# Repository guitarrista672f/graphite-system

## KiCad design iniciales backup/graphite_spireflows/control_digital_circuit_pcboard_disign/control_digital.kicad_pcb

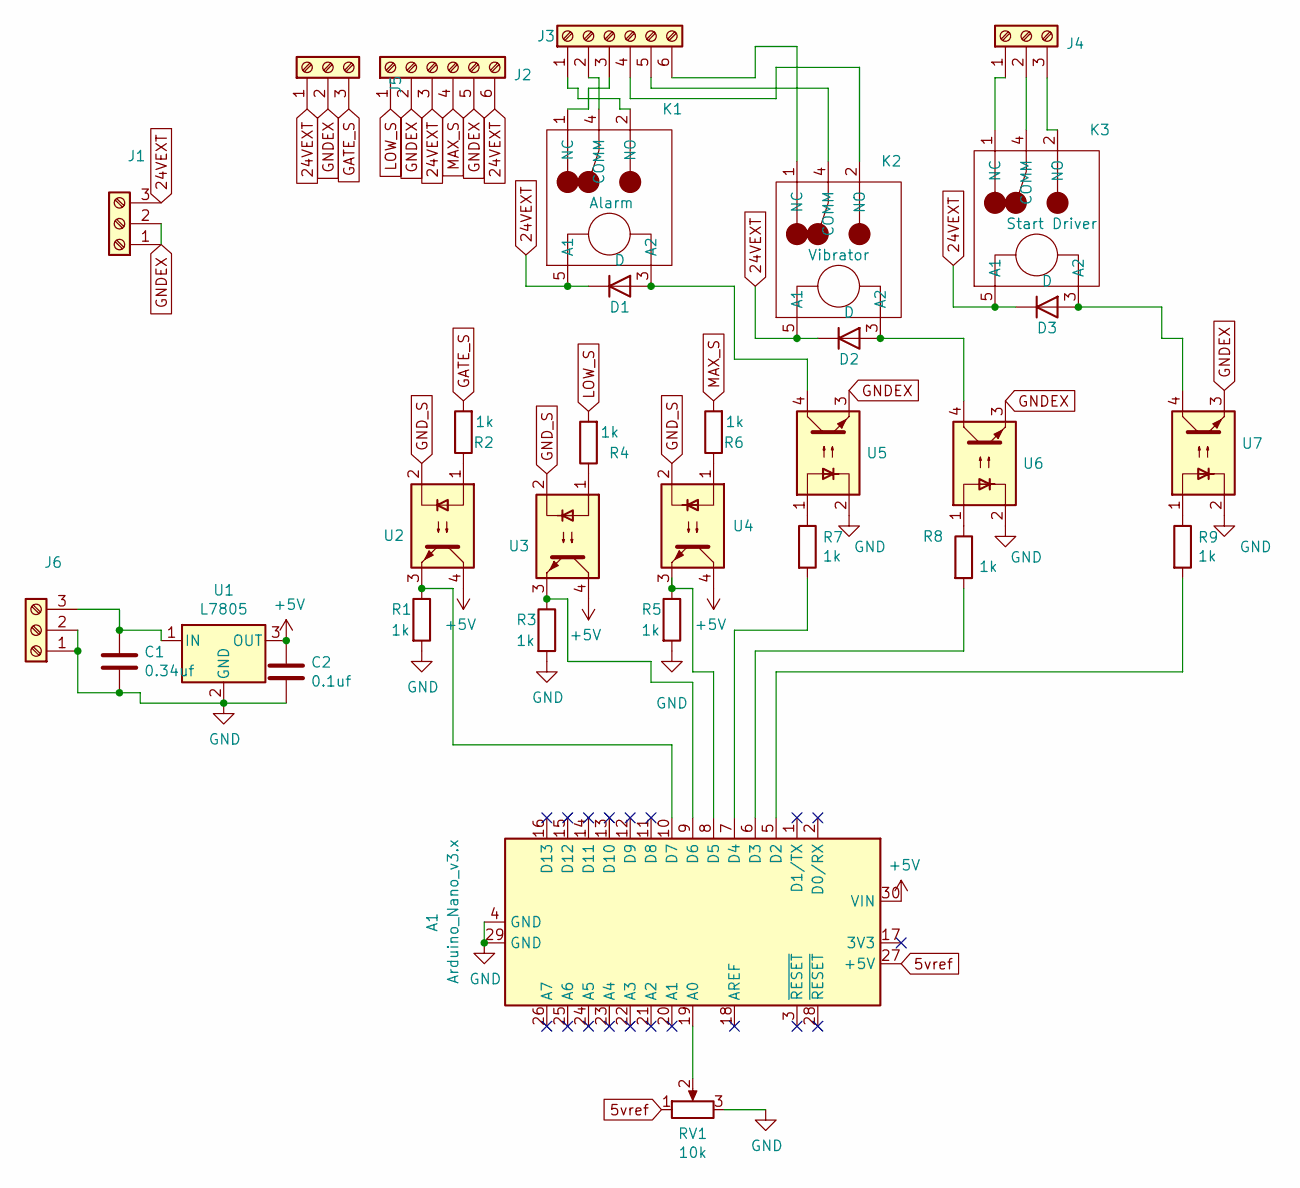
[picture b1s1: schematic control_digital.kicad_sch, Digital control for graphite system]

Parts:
A1: Arduino_Nano_v3.x; Arduino_Nano
C1: 0.34uf; CP_Radial_D6.3mm_P2.50mm
C2: 0.1uf; CP_Radial_D6.3mm_P2.50mm
D1, D2, D3: D; D_A-405_P7.62mm_Horizontal
J1, J4, J5, J6: Screw_Terminal_01x03; TerminalBlock_bornier-3_P5.08mm
J2, J3: Screw_Terminal_01x06; TerminalBlock_bornier-6_P5.08mm
K1: Alarm; SRD-24VDC-SL-C
K2: Vibrator; SRD-24VDC-SL-C
K3: Start Driver; SRD-24VDC-SL-C
R1, R2, R3, R4, R5, R6, R7, R8, R9: 1k; R_Axial_DIN0309_L9.0mm_D3.2mm_P12.70mm_Horizontal
RV1: 10k; pot_f
U1: L7805; Regulator7805
U2: SFH617A-2X016; DIP-4_W7.62mm
U3, U4, U5, U6, U7: SFH617A-2X016; DIP-4_W10.16mm

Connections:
5vref: A1.27 (+5V), RV1.1; also elsewhere on the board
24VEXT: D1.1 (K), D2.1 (K), D3.1 (K), J1.3, J2.3, J2.6, J5.1, K1.5 (A1), K2.5 (A1), K3.5 (A1)
+5V: A1.30 (VIN), C2.1, U1.3 (OUT), U2.4, U3.4, U4.4
GATE_S: J5.3, R2.2
GND: A1.4 (GND), A1.29 (GND), C1.2, C2.2, J6.1, J6.2, R1.2, R3.2, R5.2, RV1.3, U1.2 (GND), U5.2, U6.2, U7.2; also elsewhere on the board
GNDEX: J1.1, J1.2, J2.2, J2.5, J5.2, U5.3, U6.3, U7.3
GND_S: U2.2, U3.2, U4.2
LOW_S: J2.1, R4.2
MAX_S: J2.4, R6.2
unnamed: A1.5 (D2), R9.2
unnamed: A1.6 (D3), R8.2
unnamed: A1.7 (D4), R7.2
unnamed: A1.8 (D5), R5.1, U4.3
unnamed: A1.9 (D6), R3.1, U3.3
unnamed: A1.10 (D7), R1.1, U2.3
unnamed 15: A1.19 (A0), RV1.2; also elsewhere on the board
unnamed: C1.1, J6.3, U1.1 (IN)
unnamed: D1.2 (A), K1.3 (A2), U5.4
unnamed: D2.2 (A), K2.3 (A2), U6.4
unnamed: D3.2 (A), K3.3 (A2), U7.4
unnamed: J3.1, K1.2 (NO)
unnamed: J3.2, K1.4 (COMM)
unnamed: J3.3, K1.1 (NC)
unnamed: J3.4, K2.2 (NO)
unnamed: J3.5, K2.4 (COMM)
unnamed: J3.6, K2.1 (NC)
unnamed: J4.1, K3.1 (NC)
unnamed: J4.2, K3.4 (COMM)
unnamed: J4.3, K3.2 (NO)
unnamed: R2.1, U2.1
unnamed: R4.1, U3.1
unnamed: R6.1, U4.1
unnamed: R7.1, U5.1
unnamed: R8.1, U6.1
unnamed: R9.1, U7.1

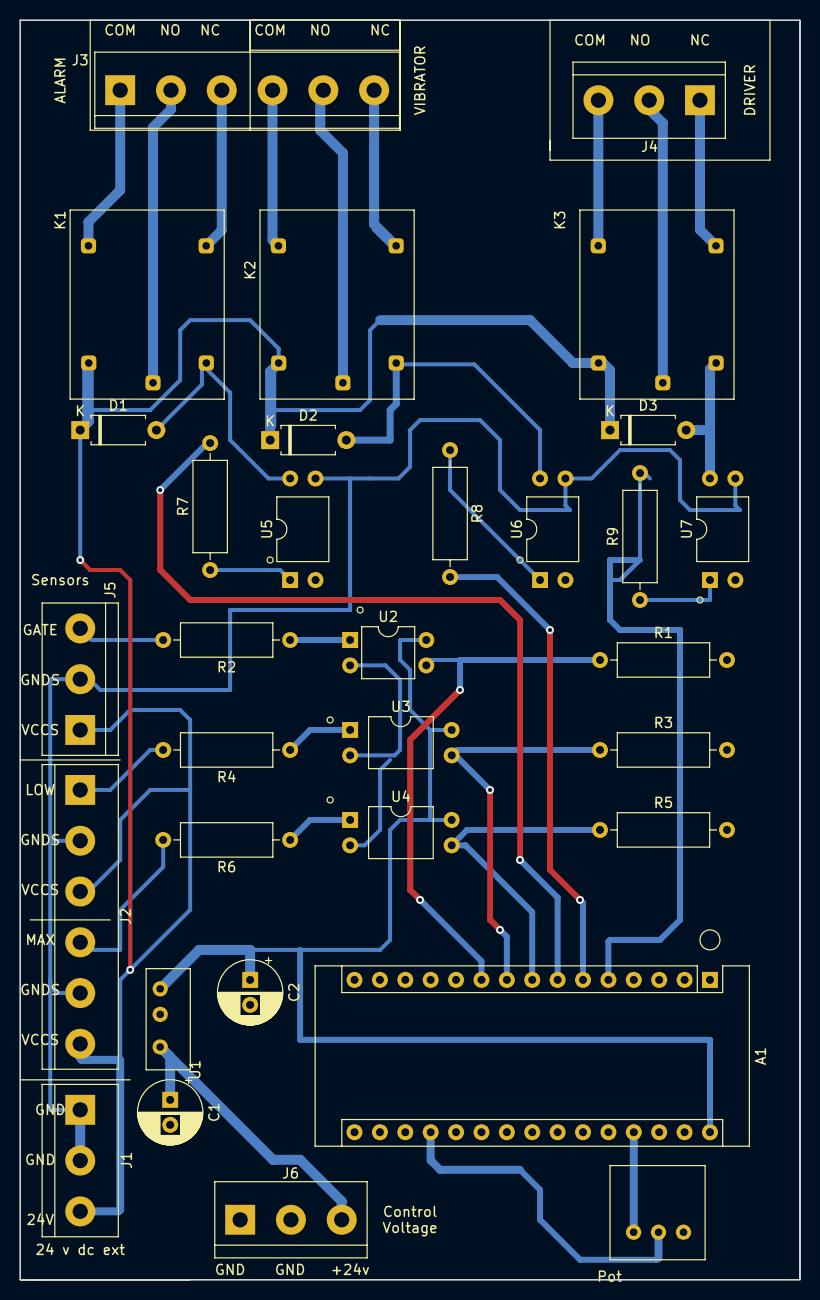
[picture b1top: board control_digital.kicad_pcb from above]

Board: 2 copper layers, 78.0 x 126.0 mm, 32 parts (0 on the bottom side), 35 nets.

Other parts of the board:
Pot: 10k; pot_f

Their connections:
5vref: Pot.1; also elsewhere on the board
GND: Pot.3; also elsewhere on the board
unnamed 15: Pot.2; also elsewhere on the board

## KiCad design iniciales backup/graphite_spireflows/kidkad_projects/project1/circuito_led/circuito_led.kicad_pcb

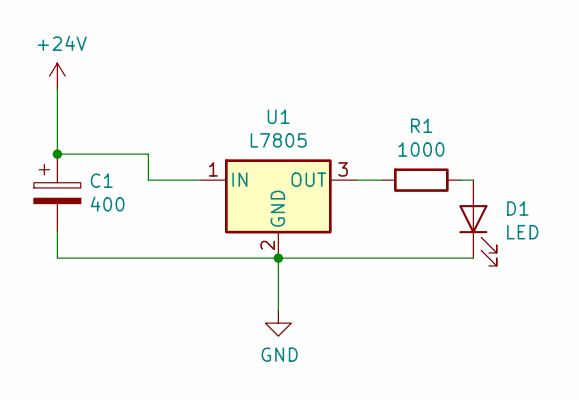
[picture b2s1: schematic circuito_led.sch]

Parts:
C1: 400; CP_Radial_D10.0mm_P3.50mm
D1: LED; LED_Oval_W5.2mm_H3.8mm
R1: 1000; R_Radial_Power_L16.1mm_W9.0mm_P7.37mm
U1: L7805; TO-220-3_Vertical

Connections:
+24V: C1.1, U1.1 (IN)
GND: C1.2, D1.1 (K), U1.2 (GND)
unnamed: D1.2 (A), R1.1
unnamed: R1.2, U1.3 (OUT)

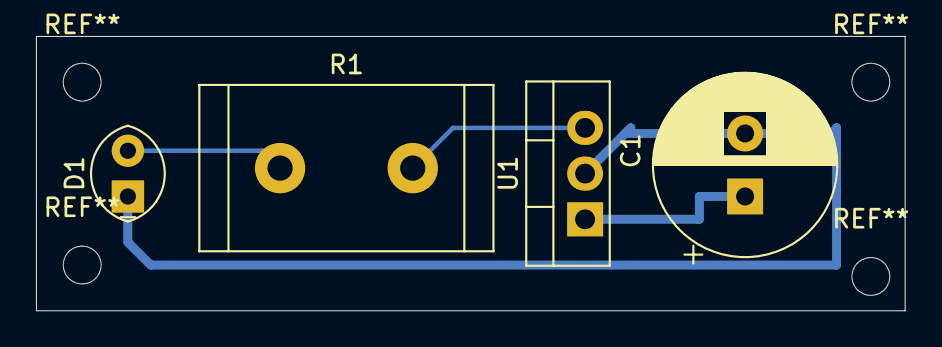
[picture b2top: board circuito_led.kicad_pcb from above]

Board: 2 copper layers, 48.3 x 15.2 mm, 4 parts (0 on the bottom side), 4 nets.

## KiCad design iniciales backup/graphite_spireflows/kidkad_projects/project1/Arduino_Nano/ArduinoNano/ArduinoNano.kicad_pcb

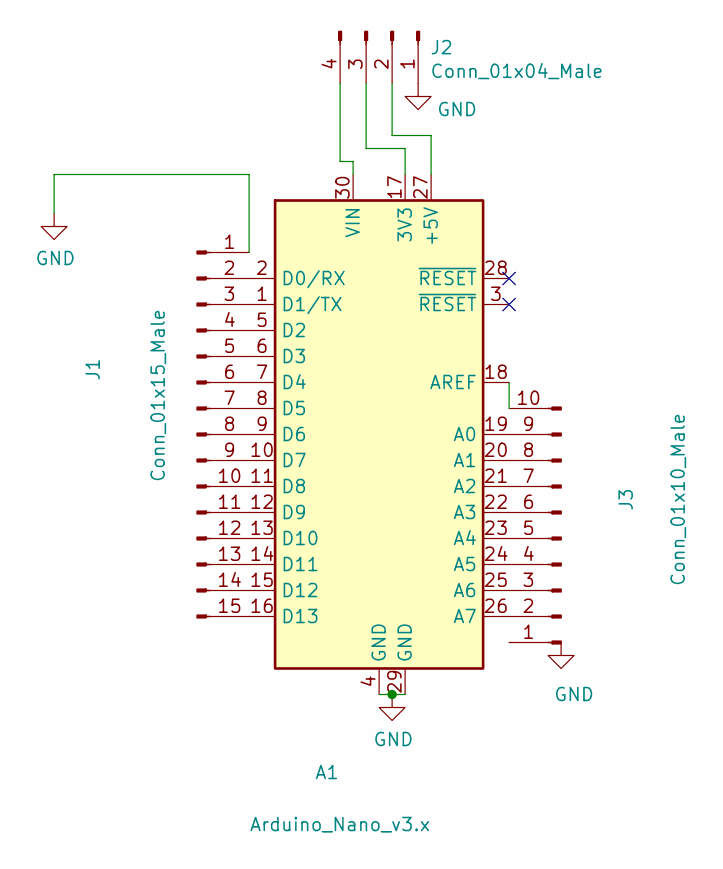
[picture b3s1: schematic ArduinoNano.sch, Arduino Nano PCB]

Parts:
A1: Arduino_Nano_v3.x; Arduino_Nano_WithMountingHoles
J1: Conn_01x15_Male; PinHeader_1x15_P2.54mm_Vertical
J2: Conn_01x04_Male; PinHeader_1x04_P2.54mm_Vertical
J3: Conn_01x10_Male; PinHeader_1x10_P2.54mm_Vertical

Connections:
GND: A1.4 (GND), A1.29 (GND), J1.1, J2.1
unnamed: A1.1 (D1/TX), J1.3
unnamed: A1.2 (D0/RX), J1.2
unnamed: A1.5 (D2), J1.4
unnamed: A1.6 (D3), J1.5
unnamed: A1.7 (D4), J1.6
unnamed: A1.8 (D5), J1.7
unnamed: A1.9 (D6), J1.8
unnamed: A1.10 (D7), J1.9
unnamed: A1.11 (D8), J1.10
unnamed: A1.12 (D9), J1.11
unnamed: A1.13 (D10), J1.12
unnamed: A1.14 (D11), J1.13
unnamed: A1.15 (D12), J1.14
unnamed: A1.16 (D13), J1.15
unnamed: A1.17 (3V3), J2.3
unnamed: A1.18 (AREF), J3.10
unnamed: A1.19 (A0), J3.9
unnamed: A1.20 (A1), J3.8
unnamed: A1.21 (A2), J3.7
unnamed: A1.22 (A3), J3.6
unnamed: A1.23 (A4), J3.5
unnamed: A1.24 (A5), J3.4
unnamed: A1.25 (A6), J3.3
unnamed: A1.26 (A7), J3.2
unnamed: A1.27 (+5V), J2.2
unnamed: A1.30 (VIN), J2.4

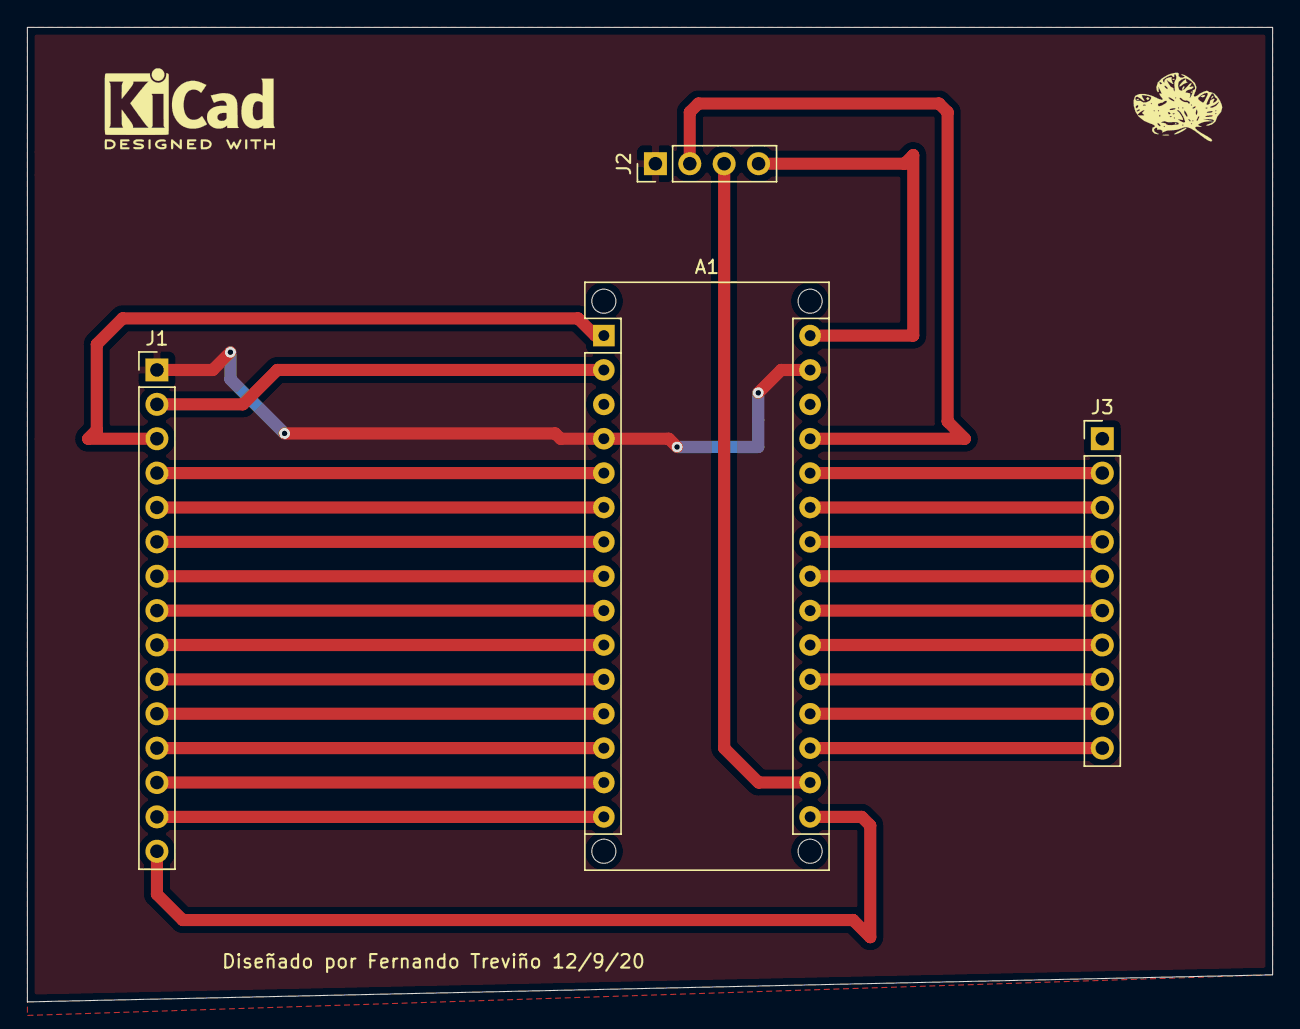
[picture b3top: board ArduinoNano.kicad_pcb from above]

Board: 2 copper layers, 92.0 x 72.0 mm, 5 parts (0 on the bottom side), 27 nets.

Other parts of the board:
ft: fam1; logo

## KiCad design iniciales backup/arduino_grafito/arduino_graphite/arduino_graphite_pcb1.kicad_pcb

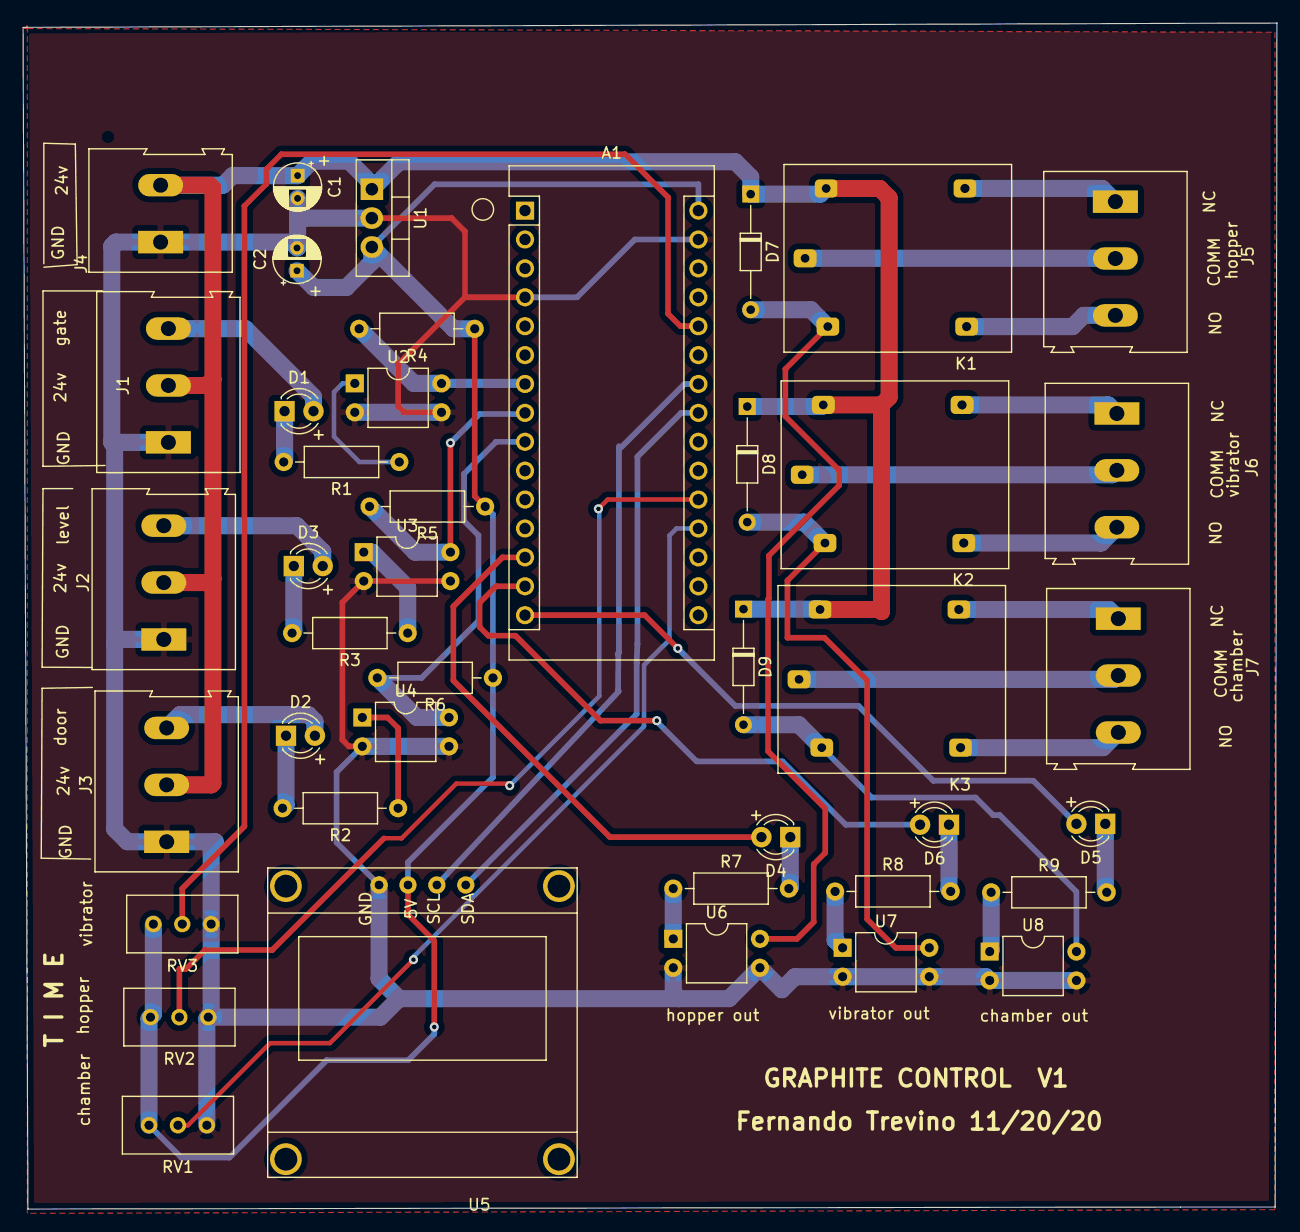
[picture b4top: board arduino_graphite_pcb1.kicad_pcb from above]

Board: 2 copper layers, 110.2 x 104.2 mm, 42 parts (0 on the bottom side), 41 nets.

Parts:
A1: Arduino_Nano_v3.x; Arduino_Nano
C1, C2: CP; capacitor
D1, D2, D3, D4, D5, D6: LED; led
D7, D8, D9: D; diode
J1, J2, J3, J5, J6, J7: Screw_Terminal_01x03; TerminalBlock_Altech_AK300-3_P5.00mm
J4: Screw_Terminal_01x02; TerminalBlock_Altech_AK300-2_P5.00mm
K1, K2, K3: srd24
R1, R2, R3, R7, R8, R9: 10k; resistor
R4, R5, R6: 1k; resistor
RV1, RV2, RV3: 1k; potensiometro
U1: L7805; 7805
U2, U3, U4, U6, U7, U8: EL817; DIP-4_W7.62mm
U5: ssd1306128x64

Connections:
+5vdc: A1.30, C2.1, R4.1, R5.1, R6.1, RV1.1, RV2.1, RV3.1, U1.3, U5.2
+24vdc: C1.1, D7.1, D8.1, D9.1, J1.2, J2.2, J3.2, J4.2, K1.1, K2.1, K3.1, U1.1
A1: A1.20, RV2.2
A4: A1.23, U5.4
A5: A1.24, U5.3
A7: A1.26, RV3.2
Ao: A1.19, RV1.2
GND: A1.4, A1.29, C1.2, C2.2, J1.1, J2.1, J3.1, J4.1, RV1.3, RV2.3, RV3.3, U1.2, U2.2, U2.3, U3.2, U3.3, U4.2, U4.3, U5.1, U6.2, U6.3, U7.2, U7.3, U8.2, U8.3
unnamed: D1.1, R1.2
unnamed: D1.2, J1.3
unnamed: D2.1, R2.2
unnamed: D2.2, J3.3
unnamed: D3.1, R3.2
unnamed: D3.2, J2.3
unnamed: D4.1, R7.2
unnamed: D5.1, R9.2
unnamed: D6.1, R8.2
unnamed: D7.2, K1.2, U6.4
unnamed: D8.2, K2.2, U7.4
unnamed: D9.2, K3.2, U8.4
unnamed: J5.1, K1.3
unnamed: J5.2, K1.4
unnamed: J5.3, K1.5
unnamed: J6.1, K2.3
unnamed: J6.2, K2.4
unnamed: J6.3, K2.5
unnamed: J7.1, K3.3
unnamed: J7.2, K3.4
unnamed: J7.3, K3.5
unnamed: R1.1, U2.1
unnamed: R2.1, U4.1
unnamed: R3.1, U3.1
unnamed: R7.1, U6.1
unnamed: R8.1, U7.1
unnamed: R9.1, U8.1
gate_hopper: A1.7, R4.2, U2.4
level_chamber: A1.8, R5.2, U3.4
out_chamber: A1.15, D5.2
out_hopper: A1.13, D4.2
out_vibrator: A1.14, D6.2
safety_doors: A1.9, R6.2, U4.4

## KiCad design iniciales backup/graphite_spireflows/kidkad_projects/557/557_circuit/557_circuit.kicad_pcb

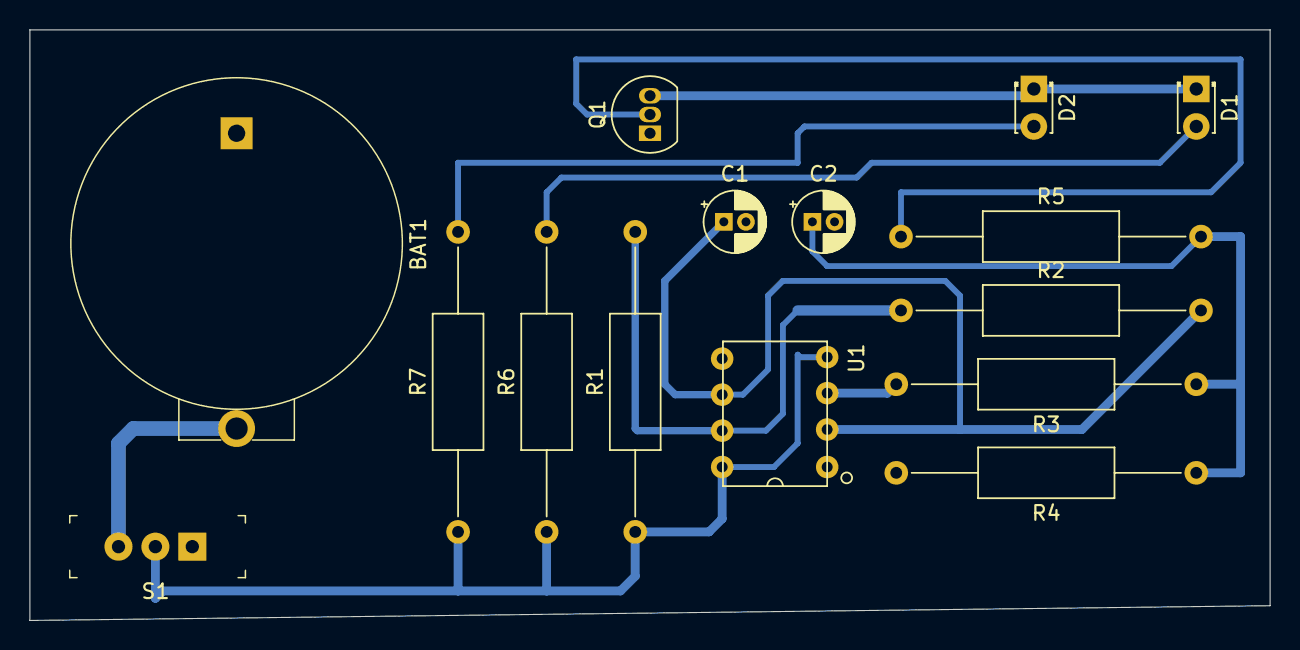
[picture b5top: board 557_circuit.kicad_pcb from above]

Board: 2 copper layers, 84.0 x 40.0 mm, 15 parts (0 on the bottom side), 11 nets.

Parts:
BAT1: BS-7; Battery_Holder_Coin_2032_BS-7
C1: 10uf; CP_Radial_D4.0mm_P1.50mm
C2: 100uf; CP_Radial_D4.0mm_P1.50mm
D1, D2: LED; LED_D1.8mm_W3.3mm_H2.4mm
Q1: 2N3904; TO-92_Inline
R1: 22k; R_Axial_DIN0309_L9.0mm_D3.2mm_P20.32mm_Horizontal
R2: 330k; R_Axial_DIN0309_L9.0mm_D3.2mm_P20.32mm_Horizontal
R3: 2.2k; R_Axial_DIN0309_L9.0mm_D3.2mm_P20.32mm_Horizontal
R4, R5: 10k; R_Axial_DIN0309_L9.0mm_D3.2mm_P20.32mm_Horizontal
R6, R7: 100; R_Axial_DIN0309_L9.0mm_D3.2mm_P20.32mm_Horizontal
S1: EG1218; Switch_Slide_11.6x4mm_EG1218
U1: 557; ICM7555-PDIP

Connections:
GND: BAT1.Neg, C1.2, C2.2, Q1.1, R4.2, U1.1
unnamed: BAT1.Pos, S1.3
unnamed: C1.1, R2.2, U1.2, U1.6
unnamed: C2.1, R3.1, R4.1, R5.2
unnamed: D1.1, D2.1, Q1.3
unnamed: D1.2, R6.2
unnamed: D2.2, R7.2
unnamed: Q1.2, R5.1
unnamed: R1.2, R2.1, U1.7
unnamed: R3.2, U1.3
VCC: R1.1, R6.1, R7.1, S1.2, U1.4, U1.8

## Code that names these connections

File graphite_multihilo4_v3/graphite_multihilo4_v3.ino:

/***********************************************************************************************************************************************
*             Usando mi inspiracion
*             10/19/2020 Michigan domingo por la noche
*             10/22/2020 agregando screen para ver las entradas analogicas de los pots.
*             11/11/20 Agregando funcion de desactivacion cuando puertas a jaula de robot son abiertas.
*************************************************************************************************************************************************/

//            Librerias para screen


#include <SPI.h>
#include <Wire.h>
#include <Adafruit_GFX.h>
#include <Adafruit_SSD1306.h>

#define SCREEN_WIDTH 128 // OLED display width, in pixels
#define SCREEN_HEIGHT 64 // OLED display height, in pixels

// Declaration for an SSD1306 display connected to I2C (SDA, SCL pins)
#define OLED_RESET     -1 //4 Reset pin # (or -1 if sharing Arduino reset pin)
Adafruit_SSD1306 display(SCREEN_WIDTH, SCREEN_HEIGHT, &Wire, OLED_RESET);



//Variables
boolean sensor_hopper;
boolean sensor_chamber;
boolean someDoorOpen=0;// Detector de Puertas en jaula robot
long lectura_pot_ch=0; //Para valores analogos chamber A0
long lectura_pot_h=0; //Para valores analogos hopper  A1
long lectura_pot_v=0; //Para valores analogos vibrador A7



//Configuracion de pines del arduino nano
 const int gate_hopper=4;
 const int level_chamber=5;
 const int safety_doors=6;
 const int output_hopper=10;
 const int output_chamber=12;
 const int output_vibrador=11;

//****** Temporizado de las tareas *********
// chamber
unsigned long tiempo_inicial=0;
unsigned long tiempo_transcurrido=0;
int chamber_bussy=0;
unsigned long timer_chamber=0;//Se actualizara con el valor del pot

 // hopper
unsigned long tiempo_inicial_h=0;
unsigned long tiempo_transcurrido_h=0;
int hopper_bussy=0;
unsigned long timer_hopper=30000; //Se actualizara con el valor del pot


// vibrador
unsigned long tiempo_inicial_v=0;
unsigned long tiempo_transcurrido_v=0;
int vibrator_bussy=0;
long timerv_on=1000; //Tiempo en estado on,modificable atraves de analogica 7
const long timerv_off=2000;//tiempo en estado off


//==============Declarando prototipo de funciones ======================
void ReadPot();
void Hopper_on();
void Hopper_off();
void Chamber_on();
void Chamber_off();
void Vibrator_on();
void Vibrator_off();
void pantalla();
void manejador_de_tareas();

//===================================================================================================================================
void setup(){
//Serial.begin(9600);
/*================================================================*/

pinMode(safety_doors,INPUT);//puertas de entrada a jaula robot
pinMode(gate_hopper,INPUT);
pinMode(output_hopper,OUTPUT);
digitalWrite(output_hopper,LOW);

pinMode(level_chamber,INPUT);
pinMode(output_chamber,OUTPUT);
digitalWrite(output_chamber,LOW);

pinMode(output_vibrador,OUTPUT);
digitalWrite(output_vibrador,LOW);
//=====================================S C R E E N  128 X 64  ========================================================
 // SSD1306_SWITCHCAPVCC = generate display voltage from 3.3V internally
display.begin(SSD1306_SWITCHCAPVCC, 0x3C);//I changed to 0x3C... Address 0x3D for 128x64
// Clear the buffer
display.clearDisplay();
//Usando Texto
display.setTextSize(1.8);
display.setTextColor(WHITE);

display.setCursor(0,0);
display.clearDisplay();
display.setCursor(10,0);//(columna,renglon)
display.println("Timers     seconds");
display.display();

display.setTextSize(1.6);
display.setCursor(10,20);
display.println("Chamber:");

display.setCursor(10,35);
display.println("Hopper:");

display.setCursor(10,50);
display.println("Vibrator:");

}

//=====================================================================================================================================

void loop(){

 manejador_de_tareas();

}

//=====================================================================================================================================

/* ========                                              F U N S I O N E S Y P R O C E S O S                   ===================== */





void Hopper_on(){
/* Is being used an opto isolator EL718 so when the sensor is high=input on opto
, the output at transistor is lower= sensor_hopper*/
sensor_hopper=digitalRead(gate_hopper);
    if (!sensor_hopper){

            digitalWrite(output_hopper,HIGH);

            hopper_bussy=1;//Establecer indicador de ocupado
            tiempo_inicial_h=millis();//Anotar tiempo de inicio
            Vibrador_on();



   }




}


void Hopper_off(){


  digitalWrite(output_hopper,LOW);
   hopper_bussy=0;

}

//=====================================================================================================================================

void Chamber_on(){

      someDoorOpen=digitalRead(safety_doors);
      if (someDoorOpen) {// Si las puertas estan cerradas =1
        sensor_chamber=digitalRead(level_chamber);
        
          /* The sensor on mix head is off when it detect lower level on graphite */
        /* it is being used opto isolator E817 so when sensor is off ,the output at transistor is on */

                     if (sensor_chamber){

                             digitalWrite(output_chamber,HIGH);

                             chamber_bussy=1;
                             tiempo_inicial=millis();

                    }
      }




}


void Chamber_off(){

  //Despues del temporizado
  digitalWrite(output_chamber,LOW);

  chamber_bussy=0;


  }

//=====================================================================================================================================

  void Vibrador_on(){
     digitalWrite(output_vibrador,HIGH);

    vibrator_bussy=1;
    tiempo_inicial_v=millis();


    }


  void Vibrador_off(){

   digitalWrite(output_vibrador,LOW);

  vibrator_bussy=0;
  tiempo_inicial_v=millis();
    }
/********************************************************************************************************************/

void manejador_de_tareas(){

  //Iniciar tareas
  ReadPot();
  Chamber_on();
  Hopper_on();
  pantalla();
  //================ CONTROL DE TIEMPOS  =========*  =========

  /*   PARA CHAMBER */
  switch (chamber_bussy){

    case 0:

    break;

    case 1://La camara se esta llenando


    tiempo_transcurrido= millis()-tiempo_inicial;

    if(tiempo_transcurrido>=timer_chamber){

        Chamber_off();

      }

    break;

    }
 //===========================================================

 /*   PARA HOPPER */
  switch (hopper_bussy){

    case 0:
    //No esta en funcion
    break;

    case 1://La Tolva se esta llenando

    tiempo_transcurrido_h= millis()-tiempo_inicial_h;
    if(tiempo_transcurrido_h>=timer_hopper){

        Hopper_off();

      }else{
        //Checar si se apago el vibrador para encenderlo nuevamente
         tiempo_transcurrido_v=millis()-tiempo_inicial_v;
        if(vibrator_bussy==0 && tiempo_transcurrido_v>=timerv_off){Vibrador_on();}

        }

    break;

    }
  //===========================================================

  /*   PARA VIBRADOR */
  switch (vibrator_bussy){

    case 0:

    break;

    case 1://vibrador funcionando

    tiempo_transcurrido_v= millis()-tiempo_inicial_v;

    if(tiempo_transcurrido_v>=timerv_on){

        Vibrador_off();

      }

    break;

    }


  }



//=====================================================================================================================================


void pantalla(){




 //display.clearDisplay(); //borra los titulos
  display.setTextSize(1.6);
  display.setCursor(80,20);
  //Para evitar el amontonamiento de pixeles
  display.setTextColor(WHITE,BLACK);//puede resivir dos parametros:color de letra,fondo
  display.println( String(lectura_pot_ch));


  display.setCursor(80,35);
  display.setTextColor(WHITE,BLACK);//
  display.println(String(lectura_pot_h));



  display.setCursor(80,50);
  display.setTextColor(WHITE,BLACK);//
  display.println(String(lectura_pot_v));
  display.display();

    }

 //==============================================================================================
void ReadPot(){

  lectura_pot_ch=map(analogRead(A0),0,1023,0,20);//Reed  analogic input A0 ,time on miliseconds, 
  timer_chamber=1000*lectura_pot_ch;  //now time is in seconds,maximum is 20 seconds


  lectura_pot_h=map(analogRead(A1),0,1023,10,600);//Leer entrada analogica A1 hopper
  timer_hopper=1000*lectura_pot_h;//maximum 6 minutes.

  //Vibrador
 lectura_pot_v=map(analogRead(A7),0,1023,0,20);//Leer entrada analogica A7
 timerv_on=1000* lectura_pot_v;

  }

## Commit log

2024-02-02 Initial project information
